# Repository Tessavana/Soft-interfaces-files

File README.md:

# Soft-interfaces-files
Sharing all circuit, PCB, code and design files to be able to replicate EOP soft interfaces
[https://softinterfaces.com/EOP.html](https://softinterfaces.com/EOP.html)

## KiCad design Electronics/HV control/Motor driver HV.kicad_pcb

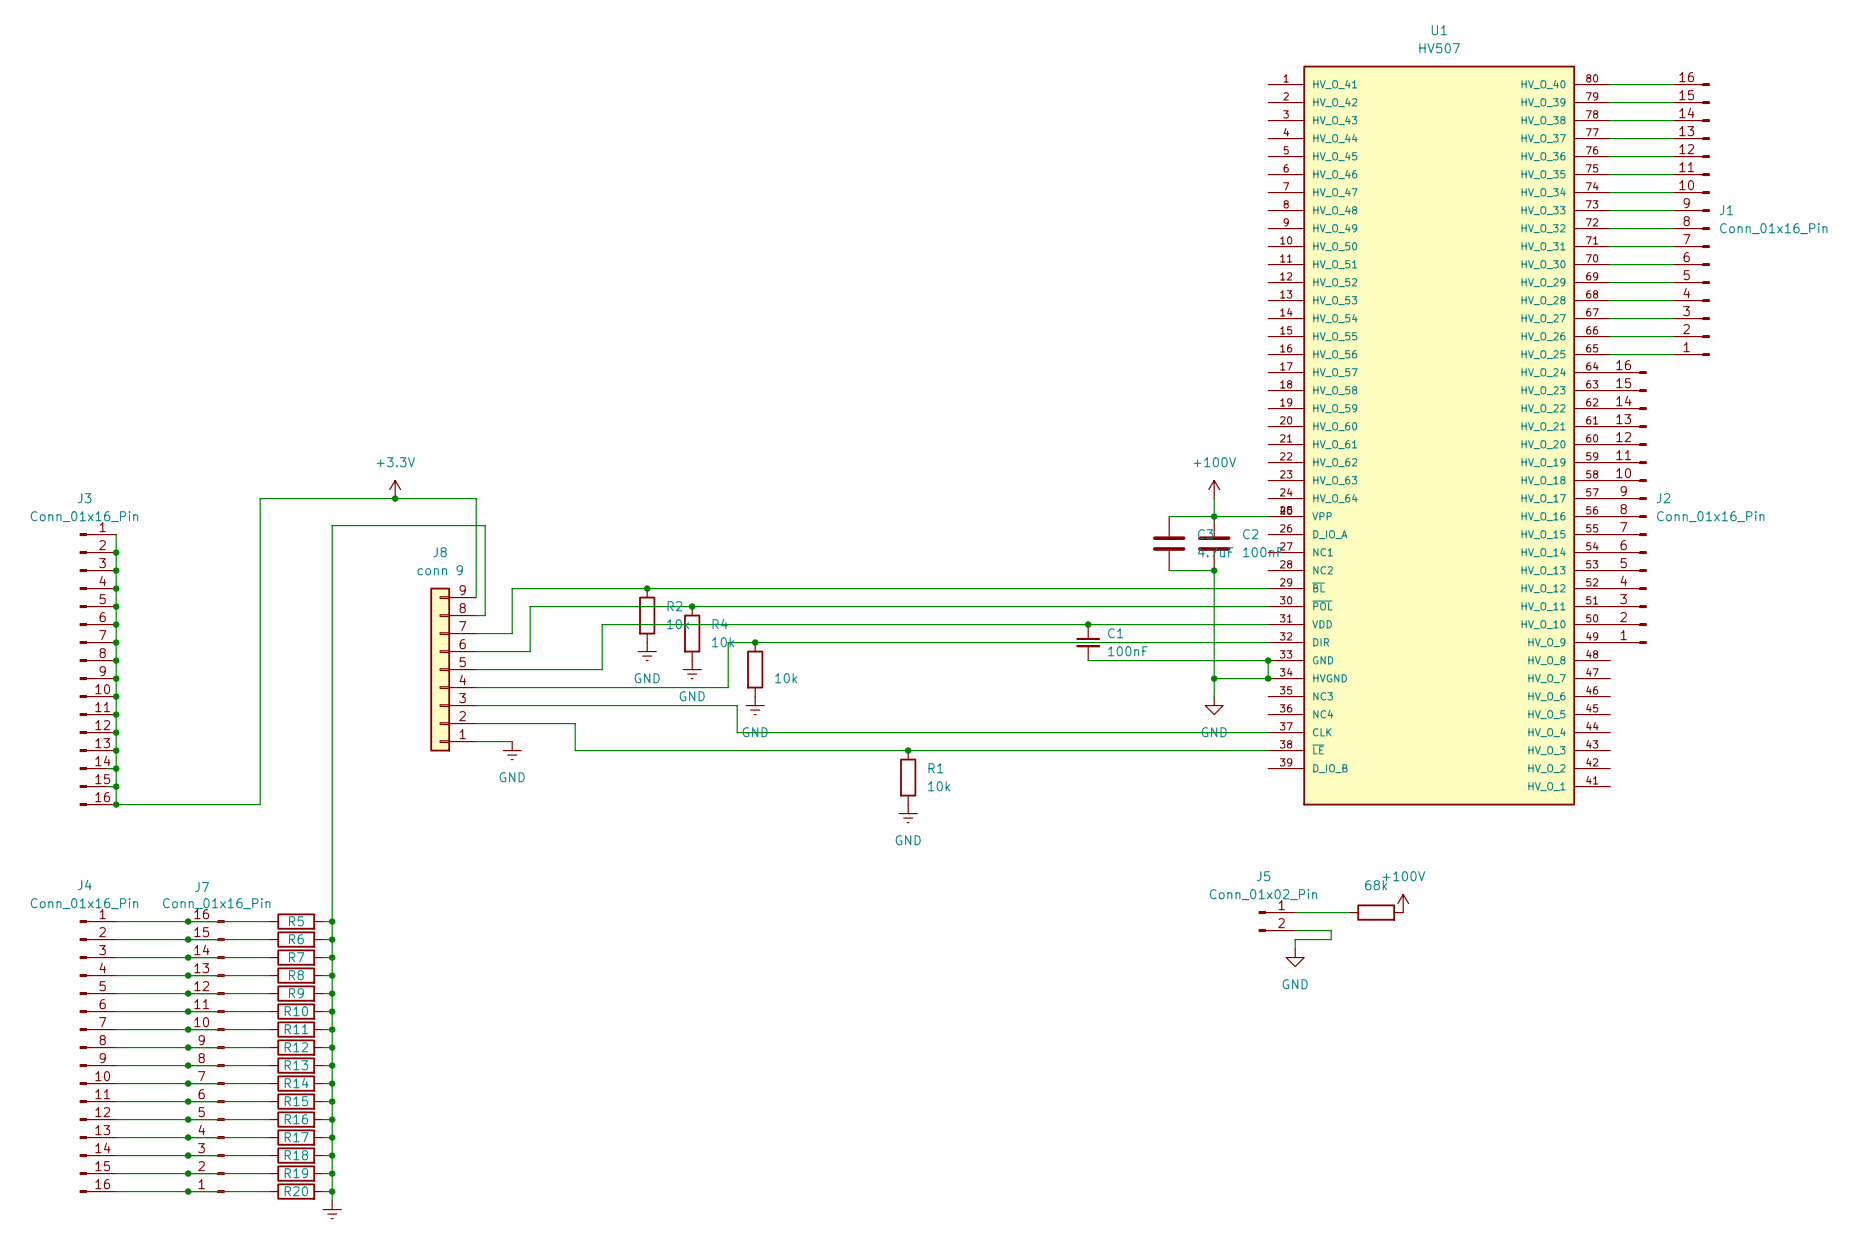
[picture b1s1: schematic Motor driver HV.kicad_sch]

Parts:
C1, C2: 100nF; C1206
C3: 4.7uF; CAP-TH_BD6.3-P2.50-D1.0-FD
J1, J2, J3, J4: Conn_01x16_Pin; FPC-SMD_16P-P1.00_XF3M1-1615-1B
J5: Conn_01x02_Pin; CONN-TH_2P-P5.00_CPC3703CTR
J7: Conn_01x16_Pin; HDR-TH_16P-P2.54-V-M
J8: conn 9; HDR-TH_9P-P2.54-V-M
R1, R2, R3, R4: 10k; R0603
R5, R6, R7, R8, R9, R10, R11, R12, R13, R14, R15, R16, R17, R18, R19, R20: 10k; R_Axial_DIN0204_L3.6mm_D1.6mm_P7.62mm_Horizontal
R21: 68k; R1206
U1: HV507; HV507PG-G

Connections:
+3.3V: J3.1, J3.2, J3.3, J3.4, J3.5, J3.6, J3.7, J3.8, J3.9, J3.10, J3.11, J3.12, J3.13, J3.14, J3.15, J3.16, J8.9
+100V: C2.1, C3.1, R21.2, U1.25 (VPP), U1.40 (VPP)
AGND: J8.8, R5.2, R6.2, R7.2, R8.2, R9.2, R10.2, R11.2, R12.2, R13.2, R14.2, R15.2, R16.2, R17.2, R18.2, R19.2, R20.2
GND: C1.2, C2.2, C3.2, J5.2, J8.1, R1.2, R2.2, R3.2, R4.2, U1.33 (GND), U1.34 (HVGND)
unnamed: J1.1, U1.65 (HV_O_25)
unnamed: J1.2, U1.66 (HV_O_26)
unnamed: J1.3, U1.67 (HV_O_27)
unnamed: J1.4, U1.68 (HV_O_28)
unnamed: J1.5, U1.69 (HV_O_29)
unnamed: J1.6, U1.70 (HV_O_30)
unnamed: J1.7, U1.71 (HV_O_31)
unnamed: J1.8, U1.72 (HV_O_32)
unnamed: J1.9, U1.73 (HV_O_33)
unnamed: J1.10, U1.74 (HV_O_34)
unnamed: J1.11, U1.75 (HV_O_35)
unnamed: J1.12, U1.76 (HV_O_36)
unnamed: J1.13, U1.77 (HV_O_37)
unnamed: J1.14, U1.78 (HV_O_38)
unnamed: J1.15, U1.79 (HV_O_39)
unnamed: J1.16, U1.80 (HV_O_40)
unnamed: J2.1, U1.49 (HV_O_9)
unnamed: J2.2, U1.50 (HV_O_10)
unnamed: J2.3, U1.51 (HV_O_11)
unnamed: J2.4, U1.52 (HV_O_12)
unnamed: J2.5, U1.53 (HV_O_13)
unnamed: J2.6, U1.54 (HV_O_14)
unnamed: J2.7, U1.55 (HV_O_15)
unnamed: J2.8, U1.56 (HV_O_16)
unnamed: J2.9, U1.57 (HV_O_17)
unnamed: J2.10, U1.58 (HV_O_18)
unnamed: J2.11, U1.59 (HV_O_19)
unnamed: J2.12, U1.60 (HV_O_20)
unnamed: J2.13, U1.61 (HV_O_21)
unnamed: J2.14, U1.62 (HV_O_22)
unnamed: J2.15, U1.63 (HV_O_23)
unnamed: J2.16, U1.64 (HV_O_24)
unnamed: J4.1, J7.16, R5.1
unnamed: J4.2, J7.15, R6.1
unnamed: J4.3, J7.14, R7.1
unnamed: J4.4, J7.13, R8.1
unnamed: J4.5, J7.12, R9.1
unnamed: J4.6, J7.11, R10.1
unnamed: J4.7, J7.10, R11.1
unnamed: J4.8, J7.9, R12.1
unnamed: J4.9, J7.8, R13.1
unnamed: J4.10, J7.7, R14.1
unnamed: J4.11, J7.6, R15.1
unnamed: J4.12, J7.5, R16.1
unnamed: J4.13, J7.4, R17.1
unnamed: J4.14, J7.3, R18.1
unnamed: J4.15, J7.2, R19.1
unnamed: J4.16, J7.1, R20.1
unnamed: J5.1, R21.1
unnamed: J8.2, R1.1, U1.38 (~LE)
unnamed: J8.3, U1.37 (CLK)
unnamed: J8.4, R3.1, U1.32 (DIR)
unnamed: C1.1, J8.5, U1.31 (VDD)
unnamed: J8.6, R4.1, U1.30 (~POL)
unnamed: J8.7, R2.1, U1.29 (~BL)

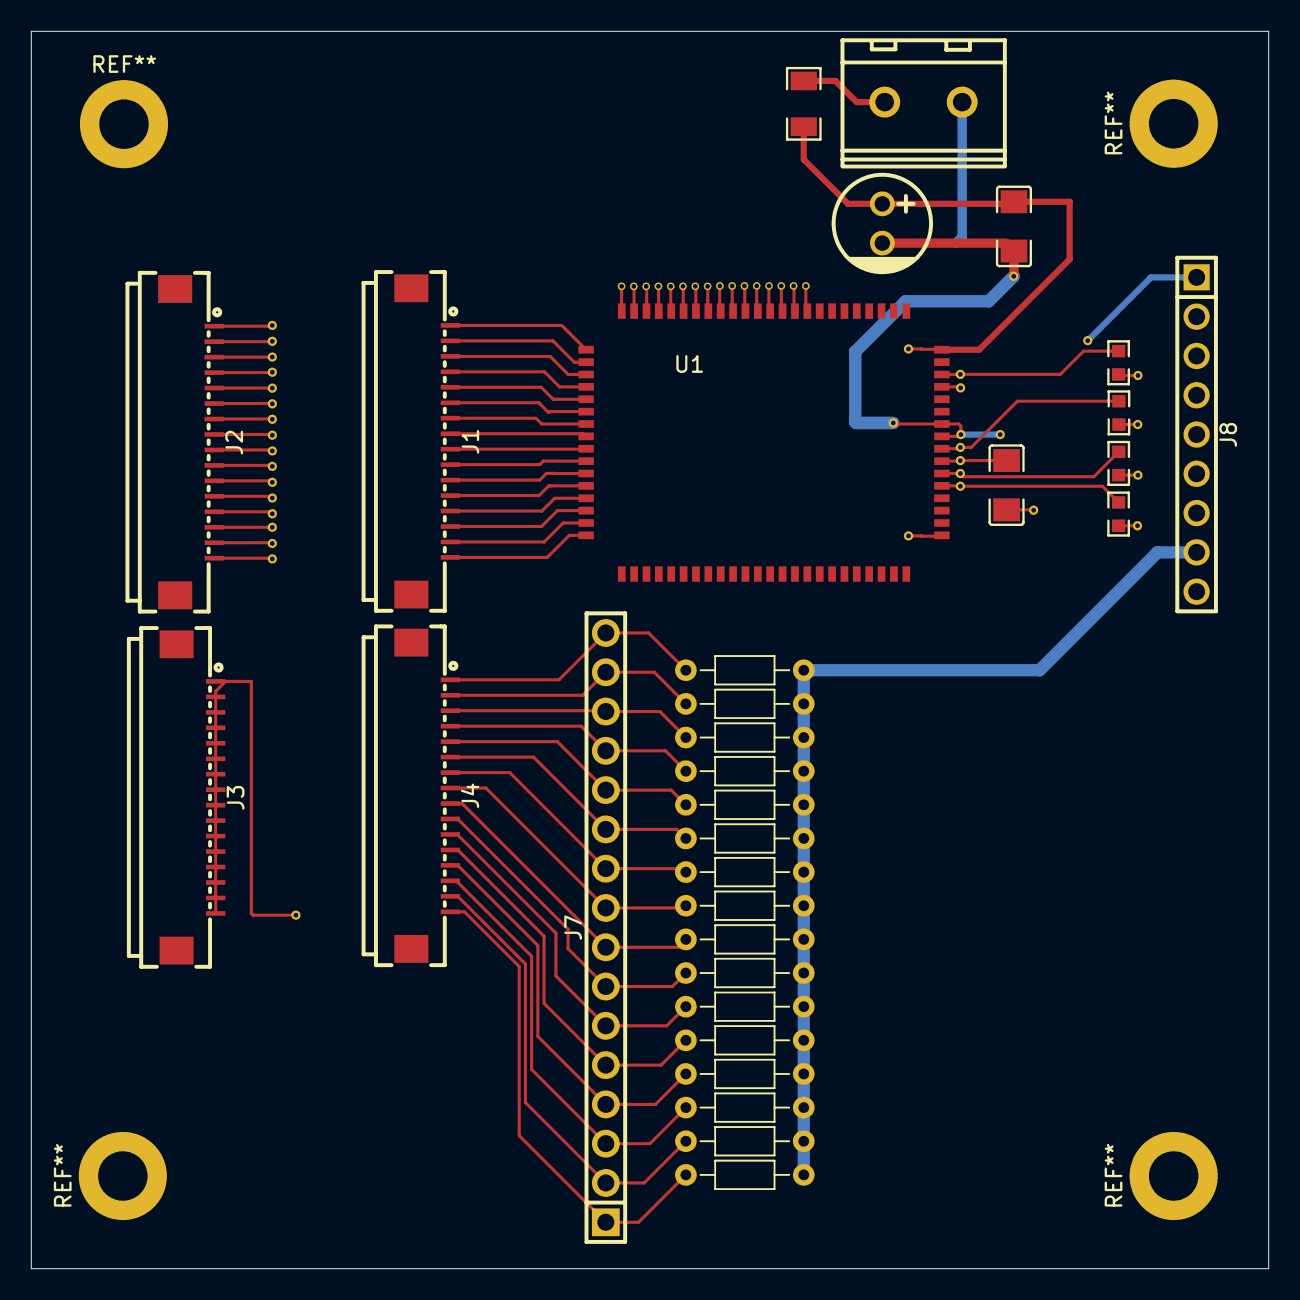
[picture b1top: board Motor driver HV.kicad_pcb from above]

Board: 4 copper layers, 80.0 x 80.0 mm, 32 parts (0 on the bottom side), 59 nets.
